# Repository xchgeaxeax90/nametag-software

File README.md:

# Datasheets and application notes:
- AVR16DD20 Datasheet: https://ww1.microchip.com/downloads/aemDocuments/documents/MCU08/ProductDocuments/DataSheets/AVR32-16DD20-14-Complete-DataSheet-DS40002413.pdf
- Generating PWM signals with TCD Appnote: https://ww1.microchip.com/downloads/aemDocuments/documents/MCU08/ApplicationNotes/ApplicationNotes/Generating-PWMSignals-Using-TCD-with-HF-Input-DS90003236C.pdf
- Getting started with TCA Technical Brief: https://ww1.microchip.com/downloads/aemDocuments/documents/MCU08/ApplicationNotes/ApplicationNotes/TB3217-Getting-Started-with-TCA-DS90003217.pdf
- Getting started with TCB Technical Brief: https://ww1.microchip.com/downloads/en/DeviceDoc/TB3214-Getting-Started-with-TCB-90003214A.pdf
- Getting started with TCD Technical Brief: https://ww1.microchip.com/downloads/aemDocuments/documents/MCU08/ApplicationNotes/ApplicationNotes/TB3212-Getting-Started-with-TCD-DS90003212.pdf
- Hacking an Attiny817XPlained to be a UPDI programmer: https://www.jsykora.info/2019/04/avr-updi-programmer-from-attiny817-xplained-mini/

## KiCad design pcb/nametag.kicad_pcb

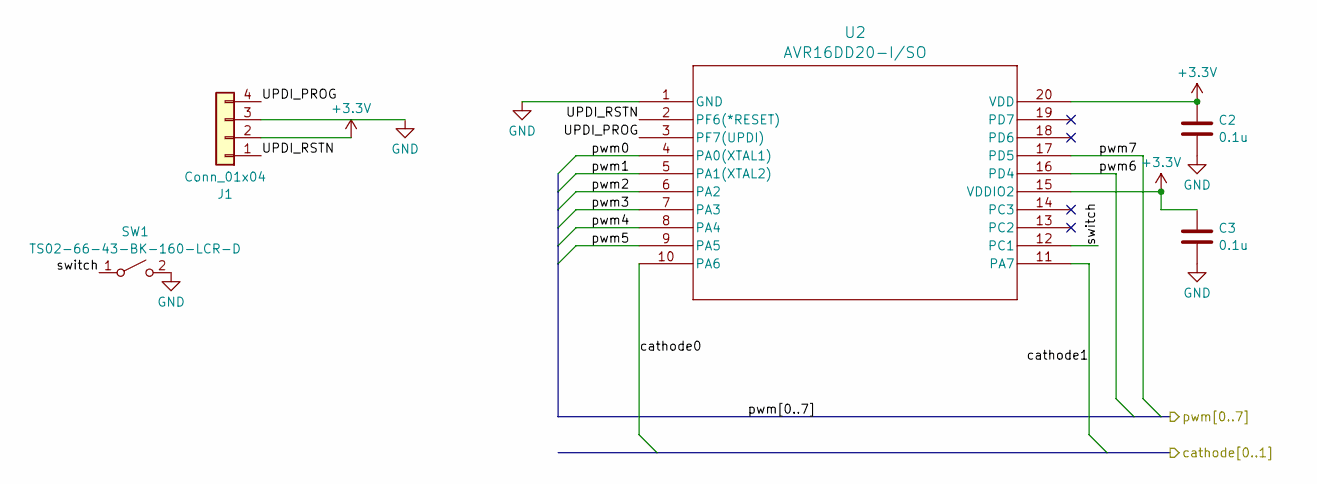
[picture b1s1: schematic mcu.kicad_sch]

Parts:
C2, C3: 0.1u; C_0603_1608Metric_Pad1.08x0.95mm_HandSolder
J1: Conn_01x04; PinSocket_1x04_P2.54mm_Vertical
SW1: TS02-66-43-BK-160-LCR-D; SW_PUSH_6mm_H4.3mm
U2: AVR16DD20-I/SO; SOIC-20W_7.5x12.8mm_P1.27mm

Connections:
+3.3V: C2.1, C3.1, J1.2, U2.15 (VDDIO2), U2.20 (VDD); also elsewhere on the board
/Mcu/UPDI_PROG: J1.4, U2.3 (PF7(UPDI))
/Mcu/UPDI_RSTN: J1.1, U2.2 (PF6(*RESET))
/Mcu/cathode0: U2.10 (PA6); also elsewhere on the board
/Mcu/cathode1: U2.11 (PA7); also elsewhere on the board
/Mcu/pwm0: U2.4 (PA0(XTAL1)); also elsewhere on the board
/Mcu/pwm1: U2.5 (PA1(XTAL2)); also elsewhere on the board
/Mcu/pwm2: U2.6 (PA2); also elsewhere on the board
/Mcu/pwm3: U2.7 (PA3); also elsewhere on the board
/Mcu/pwm4: U2.8 (PA4); also elsewhere on the board
/Mcu/pwm5: U2.9 (PA5); also elsewhere on the board
/Mcu/pwm6: U2.16 (PD4); also elsewhere on the board
/Mcu/pwm7: U2.17 (PD5); also elsewhere on the board
/Mcu/switch: SW1.1 (A), U2.12 (PC1)
GND: C2.2, C3.2, J1.3, SW1.2 (B), U2.1 (GND); also elsewhere on the board

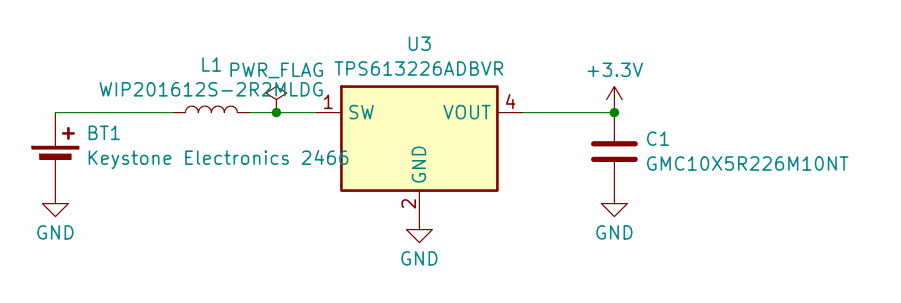
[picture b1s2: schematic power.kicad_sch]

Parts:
BT1: Keystone Electronics 2466; BatteryHolder_Keystone_2466_1xAAA
C1: GMC10X5R226M10NT; C_0603_1608Metric_Pad1.08x0.95mm_HandSolder
L1: WIP201612S-2R2MLDG; L_0805_2012Metric_Pad1.15x1.40mm_HandSolder
U3: TPS613226ADBVR; SOT-23-5

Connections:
+3.3V: C1.1, U3.4 (VOUT); also elsewhere on the board
GND: BT1.2 (-), C1.2, U3.2 (GND); also elsewhere on the board
unnamed: BT1.1 (+), L1.1
unnamed: L1.2, U3.1 (SW)

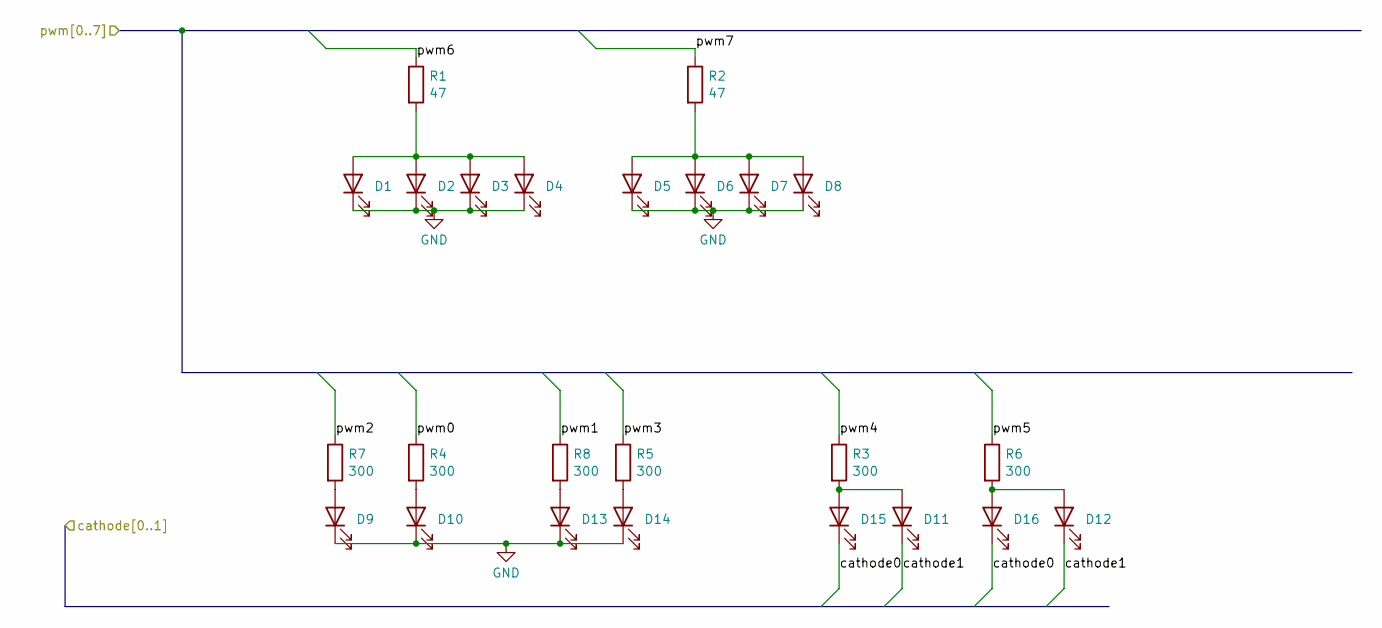
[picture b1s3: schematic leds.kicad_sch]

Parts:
D1, D2, D3, D4, D5, D6, D7, D8: LTST-C190KFKT; LED_0603_1608Metric_Pad1.05x0.95mm_HandSolder
D9, D10, D11, D12, D13, D14: SMLD12E3N1WT86; LED_0603_1608Metric_Pad1.05x0.95mm_HandSolder
D15, D16: SMLD12E2N1WT86; LED_0603_1608Metric_Pad1.05x0.95mm_HandSolder
R1, R2: 47; R_0603_1608Metric_Pad0.98x0.95mm_HandSolder
R3, R4, R5, R6, R7, R8: 300; R_0603_1608Metric_Pad0.98x0.95mm_HandSolder

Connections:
/Mcu/cathode0: D15.1 (K), D16.1 (K); also elsewhere on the board
/Mcu/cathode1: D11.1 (K), D12.1 (K); also elsewhere on the board
/Mcu/pwm0: R4.1; also elsewhere on the board
/Mcu/pwm1: R8.1; also elsewhere on the board
/Mcu/pwm2: R7.1; also elsewhere on the board
/Mcu/pwm3: R5.1; also elsewhere on the board
/Mcu/pwm4: R3.1; also elsewhere on the board
/Mcu/pwm5: R6.1; also elsewhere on the board
/Mcu/pwm6: R1.1; also elsewhere on the board
/Mcu/pwm7: R2.1; also elsewhere on the board
GND: D1.1 (K), D2.1 (K), D3.1 (K), D4.1 (K), D5.1 (K), D6.1 (K), D7.1 (K), D8.1 (K), D9.1 (K), D10.1 (K), D13.1 (K), D14.1 (K); also elsewhere on the board
unnamed: D1.2 (A), D2.2 (A), D3.2 (A), D4.2 (A), R1.2
unnamed: D5.2 (A), D6.2 (A), D7.2 (A), D8.2 (A), R2.2
unnamed: D9.2 (A), R7.2
unnamed: D10.2 (A), R4.2
unnamed: D11.2 (A), D15.2 (A), R3.2
unnamed: D12.2 (A), D16.2 (A), R6.2
unnamed: D13.2 (A), R8.2
unnamed: D14.2 (A), R5.2

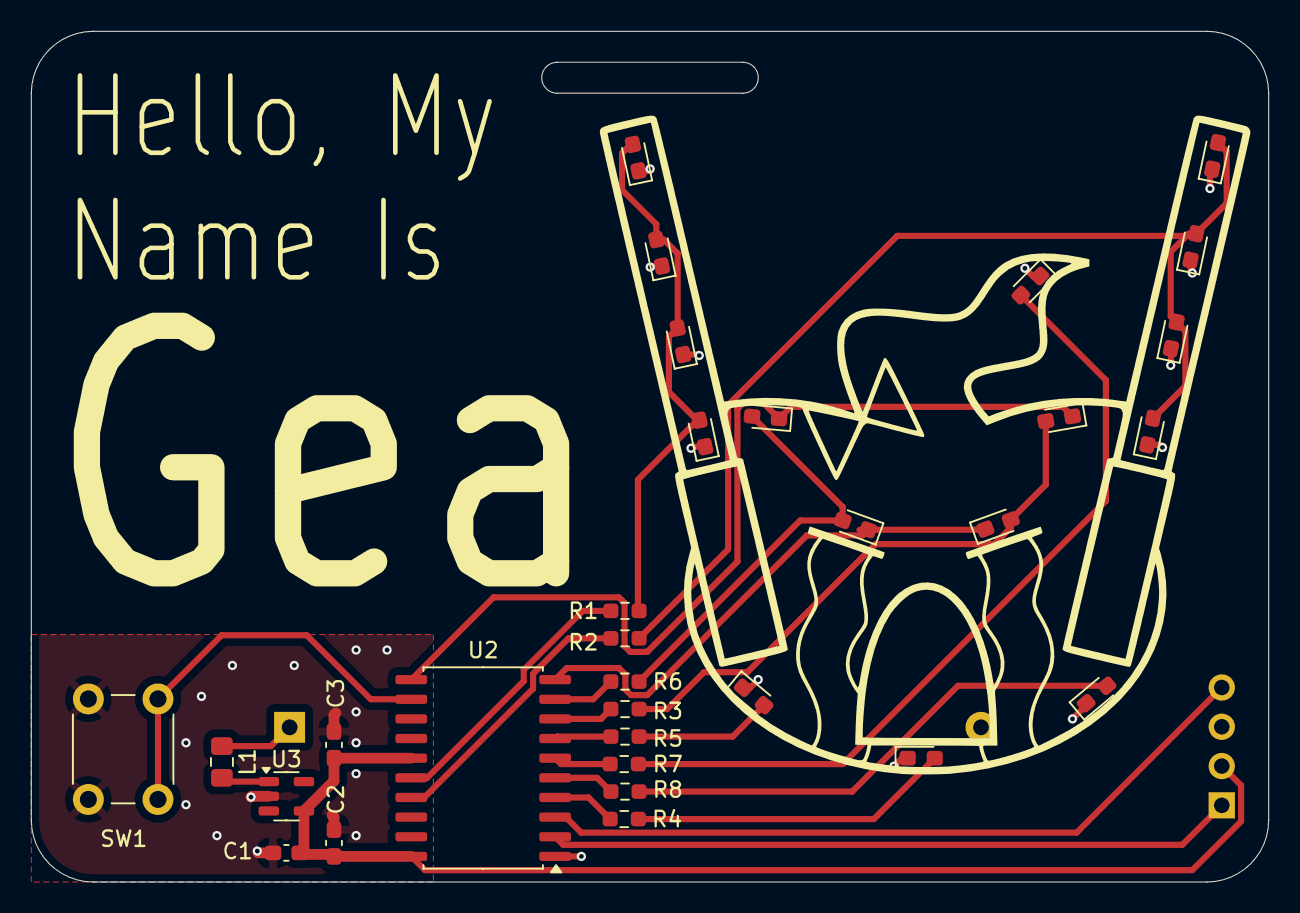
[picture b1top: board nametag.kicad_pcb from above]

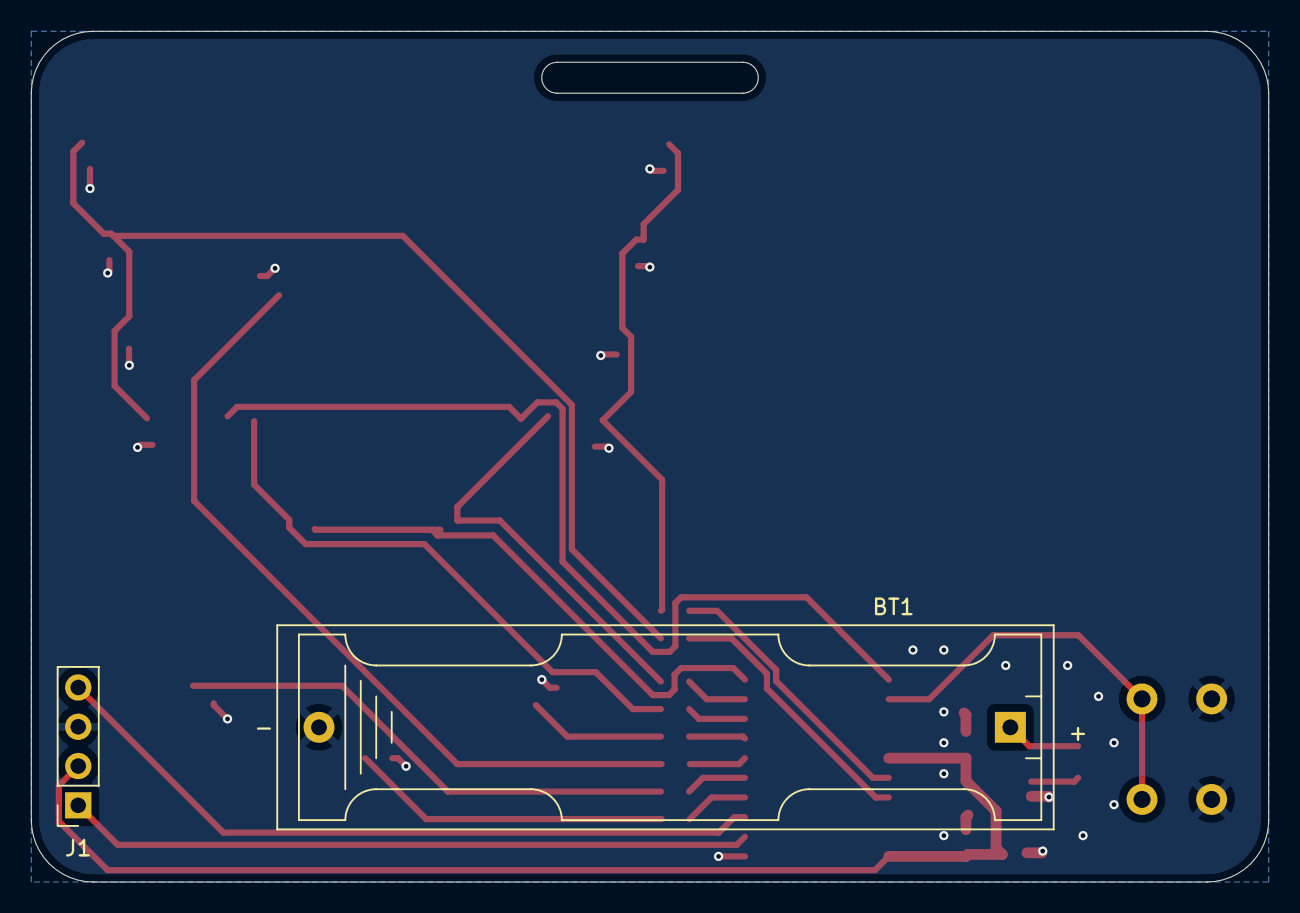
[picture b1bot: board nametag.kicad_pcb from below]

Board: 2 copper layers, 80.0 x 55.0 mm, 33 parts (2 on the bottom side), 25 nets.

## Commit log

2024-11-03 Initial commit, working on skeleton without part to test on
2024-11-04 Separate out pwm functions into their own file
2024-11-04 Set timer B as periodic interrupt, drive the multiplex select pins on an interrupt
2024-11-04 Configure a pin change update for the button input
2024-11-05 Working pwm on both face and light sticks
2024-11-05 Add animations
2024-11-05 Make a better animation, actually store it in flash
2024-11-05 Fix animation multiplex bug
2024-11-05 Add selectable animations
2024-11-05 Add brightness adjustment and state machine
2024-11-05 Add sleep mode
2024-11-06 Make brightness controls more obvious
2024-11-06 Tweaks to hopefully reduce power consumption
2024-11-06 Add some more animations
2024-11-09 Move ISR function out of timer.c
2024-11-23 Make power off take effect immediately
2024-12-17 Move sources to src/ folder
2024-12-17 Add kicad project to repo
2024-12-17 Add gerber outputs
2024-12-17 Add prebuilt main.hex
2024-12-17 Add readme
2024-12-17 Add image
2024-12-17 Add PDF schematic and description of how to affix nametag
